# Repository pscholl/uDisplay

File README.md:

bluetoothdisplay
================

Miniature Bluetooth Display

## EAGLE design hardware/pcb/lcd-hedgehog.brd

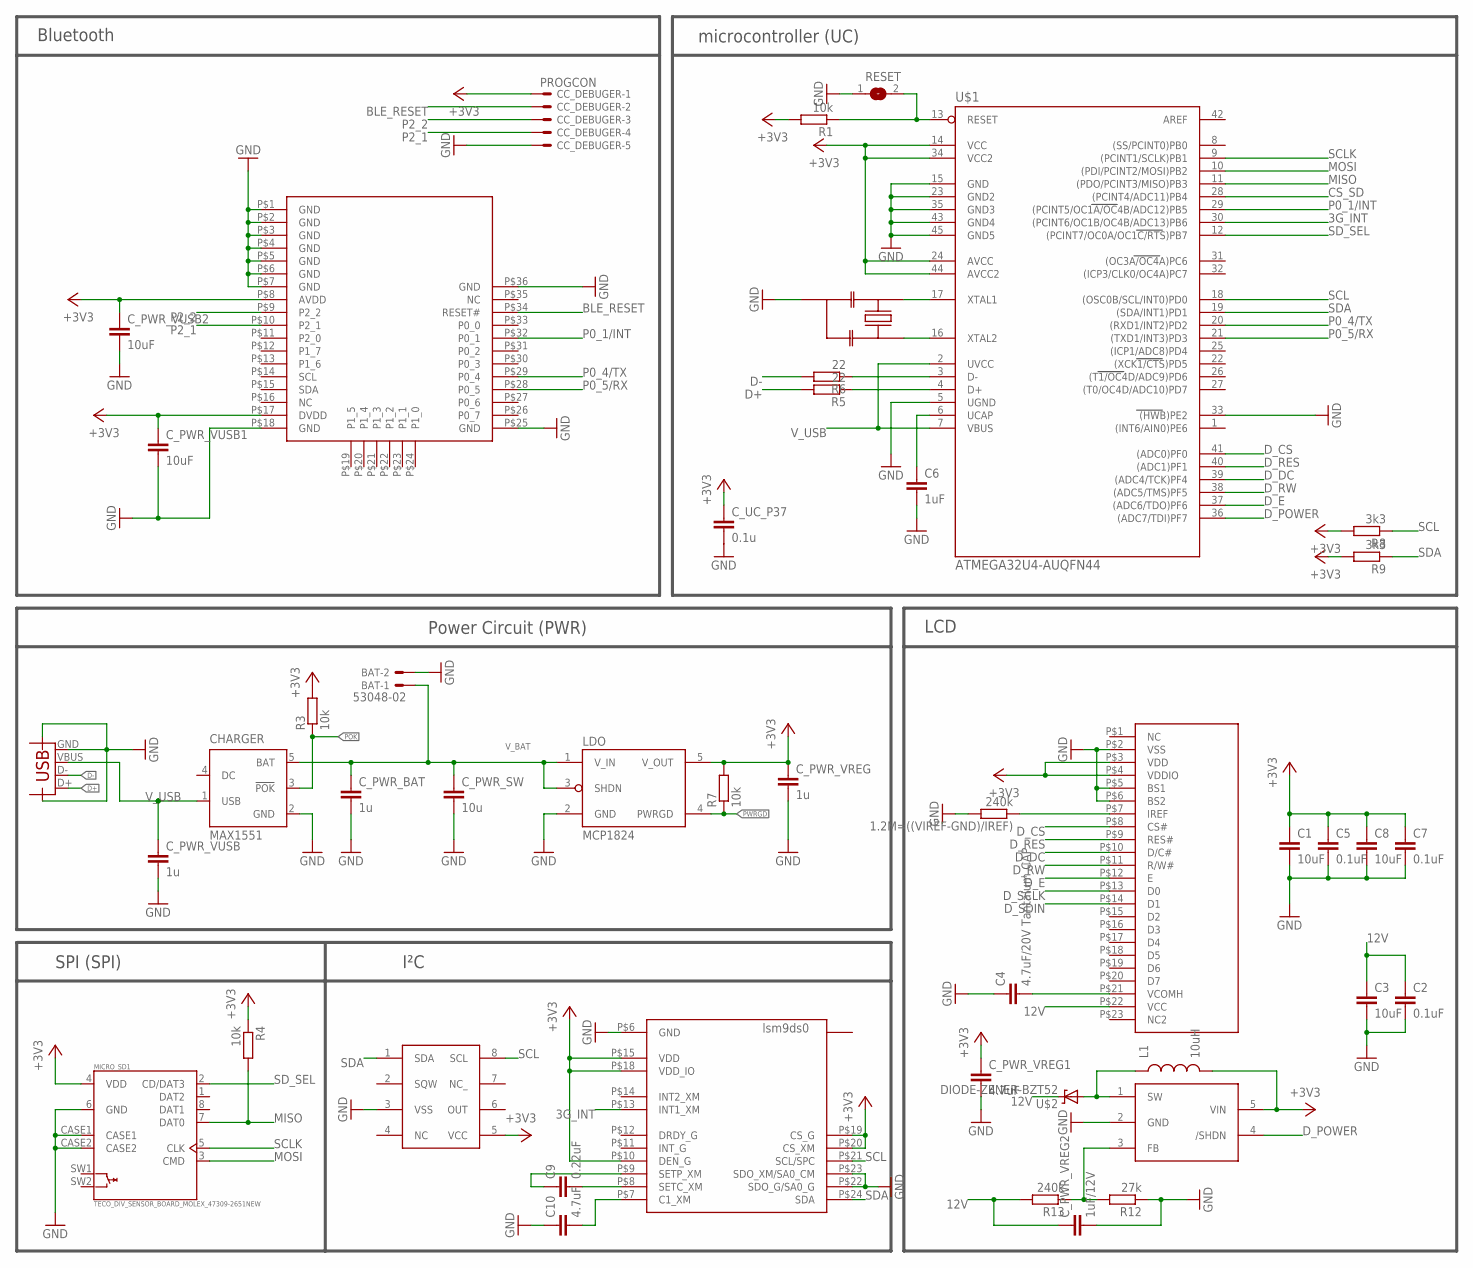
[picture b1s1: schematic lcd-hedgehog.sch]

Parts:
1.2M=((VIREF-GND)/IREF): 240k; R0603
12MHZ_RESONATOR: RESONATORPRQC-S; PRQC
BAT: 53048-02
C1, C3, C8: 10uF; C0603K
C2, C5, C7: 0.1uF; C0603K
C4: 4.7uF/20V Tantalum CAP; C0603K
C6: 1uF; C0603K
C9: 0.22uF; C0603K
C10: 4.7uF; C0603K
CC_DEBUGER: PROGCON; 53047-05-OCT
CHARGER: MAX1551; SOT23-5L
C_PWR_BAT: 1u; C0603K
C_PWR_SW: 10u; C0805K
C_PWR_VREG: 1u; C0603K
C_PWR_VREG1: 4.7uF; C0603K
C_PWR_VREG2: 1uF/12V; C0603K
C_PWR_VUSB: 1u; C0603K
C_PWR_VUSB1, C_PWR_VUSB2: 10uF; C0603K
C_UC_P37: 0.1u; C0603K
L1: 10uH; SPARKFUN_0603
LDO: MCP1824; SOT-23-5
MICRO_SD1: TECO_DIV_SENSOR_BOARD_MOLEX_47309-2651NEW; TECO_DIV_SENSOR_BOARD_MOLEX_47309-2651
R1, R3, R4, R7: 10k; R0603
R5, R6: 22; R0603
R8, R9: 3k3; R0603
R12: 27k; R0603
R13: 240k; R0603
RESET: SJ
U$1: ATMEGA32U4-AUQFN44; QFN44
U$2: DIODE-ZENER-BZT52; SOD-323
U$3: STUFF_M41T62; STUFF_M41T62LC6F
U$4: SFV23
U$5: LM2703; SOT-23-5
U$6: BLE113-A
U$7: LSM9D; LGA4X4
X1: SPARKFUN_USB-MICROB

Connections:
3G_INT: U$1.30 ((PCINT6/OC1B/OC4B/ADC13)PB6), U$7.P$13 (INT1_XM)
12V: C2.1, C3.1, C_PWR_VREG2.1, R13.2, U$2.1 (C), U$4.P$22 (VCC)
+3V3: C1.1, C5.1, C7.1, C8.1, CC_DEBUGER.1, C_PWR_VREG.1, C_PWR_VREG1.1, C_PWR_VUSB1.1, C_PWR_VUSB2.1, C_UC_P37.1, L1.2, LDO.5 (V_OUT), MICRO_SD1.4 (VDD), R1.2, R3.2, R4.1, R7.2, R8.2, R9.2, U$1.14 (VCC), U$1.24 (AVCC), U$1.34 (VCC2), U$1.44 (AVCC2), U$3.5 (VCC), U$4.P$3 (VDD), U$4.P$4 (VDDIO), U$5.5 (VIN), U$6.P$8 (AVDD), U$6.P$17 (DVDD), U$7.P$10 (DEN_G), U$7.P$15 (VDD), U$7.P$18 (VDD_IO), U$7.P$19 (CS_G), U$7.P$20 (CS_XM)
BLE_RESET: CC_DEBUGER.2, U$6.P$34 (RESET#)
CS_SD: U$1.28 ((PCINT4/ADC11)PB4)
D+: R5.2, X1.D+
D-: R6.2, X1.D-
D_CS: U$1.41 ((ADC0)PF0), U$4.P$8 (CS#)
D_DC: U$1.39 ((ADC4/TCK)PF4), U$4.P$10 (D/C#)
D_E: U$1.37 ((ADC6/TDO)PF6), U$4.P$12 (E)
D_POWER: U$1.36 ((ADC7/TDI)PF7), U$5.4 (/SHDN)
D_RES: U$1.40 ((ADC1)PF1), U$4.P$9 (RES#)
D_RW: U$1.38 ((ADC5/TMS)PF5), U$4.P$11 (R/W#)
D_SCLK: U$4.P$13 (D0)
D_SDIN: U$4.P$14 (D1)
GND: 1.2M=((VIREF-GND)/IREF).2, 12MHZ_RESONATOR.GND, BAT.2, C1.2, C2.2, C3.2, C4.1, C5.2, C6.2, C7.2, C8.2, C10.1, CC_DEBUGER.5, CHARGER.2 (GND), C_PWR_BAT.2, C_PWR_SW.2, C_PWR_VREG.2, C_PWR_VREG1.2, C_PWR_VREG2.2, C_PWR_VUSB.2, C_PWR_VUSB1.2, C_PWR_VUSB2.2, C_UC_P37.2, LDO.2 (GND), MICRO_SD1.6 (GND), MICRO_SD1.CASE1, MICRO_SD1.CASE2, R12.1, RESET.1, U$1.5 (UGND), U$1.15 (GND), U$1.23 (GND2), U$1.33 ((HWB)PE2), U$1.35 (GND3), U$1.43 (GND4), U$1.45 (GND5), U$3.3 (VSS), U$4.P$2 (VSS), U$4.P$5 (BS1), U$4.P$6 (BS2), U$5.2 (GND), U$6.P$1 (GND), U$6.P$2 (GND), U$6.P$3 (GND), U$6.P$4 (GND), U$6.P$5 (GND), U$6.P$6 (GND), U$6.P$7 (GND), U$6.P$18 (GND), U$6.P$25 (GND), U$6.P$36 (GND), U$7.P$5 (GND), U$7.P$22 (SDO_G/SA0_G), U$7.P$23 (SDO_XM/SA0_CM), X1.GND, X1.GND@2 (CASE), X1.GND@3 (CASE)
MISO: MICRO_SD1.7 (DAT0), R4.2, U$1.11 ((PDO/PCINT3/MISO)PB3)
MOSI: MICRO_SD1.3 (CMD), U$1.10 ((PDI/PCINT2/MOSI)PB2)
unnamed: R1.1, RESET.2, U$1.13 (RESET)
unnamed: 12MHZ_RESONATOR.2, U$1.17 (XTAL1)
unnamed: 12MHZ_RESONATOR.1, U$1.16 (XTAL2)
unnamed: R6.1, U$1.3 (D-)
unnamed: R5.1, U$1.4 (D+)
unnamed: C9.2, U$7.P$8 (SETC_XM)
unnamed: C9.1, U$7.P$9 (SETP_XM)
unnamed: C10.2, U$7.P$7 (C1_XM)
unnamed: C6.1, U$1.6 (UCAP)
unnamed: R12.2, R13.1, U$5.3 (FB)
unnamed: L1.1, U$2.2 (A), U$5.1 (SW)
unnamed: C4.2, U$4.P$21 (VCOMH)
unnamed: 1.2M=((VIREF-GND)/IREF).1, U$4.P$7 (IREF)
P0_1/INT: U$1.29 ((PCINT5/OC1A/OC4B/ADC12)PB5), U$6.P$32 (P0_1)
P0_4/TX: U$1.20 ((RXD1/INT2)PD2), U$6.P$29 (P0_4)
P0_5/RX: U$1.21 ((TXD1/INT3)PD3), U$6.P$28 (P0_5)
P2_1: CC_DEBUGER.4, U$6.P$10 (P2_1)
P2_2: CC_DEBUGER.3, U$6.P$9 (P2_2)
POK: CHARGER.3 (!POK), R3.1
PWRGD: LDO.4 (PWRGD), R7.1
SCL: R8.1, U$1.18 ((OSC0B/SCL/INT0)PD0), U$3.8 (SCL), U$7.P$21 (SCL/SPC)
SCLK: MICRO_SD1.5 (CLK), U$1.9 ((PCINT1/SCLK)PB1)
SDA: R9.1, U$1.19 ((SDA/INT1)PD1), U$3.1 (SDA), U$7.P$24 (SDA)
SD_SEL: MICRO_SD1.2 (CD/DAT3), U$1.12 ((PCINT7/OC0A/OC1C/RTS)PB7)
V_BAT: BAT.1, CHARGER.5 (BAT), C_PWR_BAT.1, C_PWR_SW.1, LDO.1 (V_IN), LDO.3 (SHDN)
V_USB: CHARGER.1 (USB), C_PWR_VUSB.1, U$1.2 (UVCC), U$1.7 (VBUS), X1.VBUS

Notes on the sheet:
Power Circuit (PWR)
SPI (SPI)
microcontroller (UC)
LCD
Bluetooth
I²C

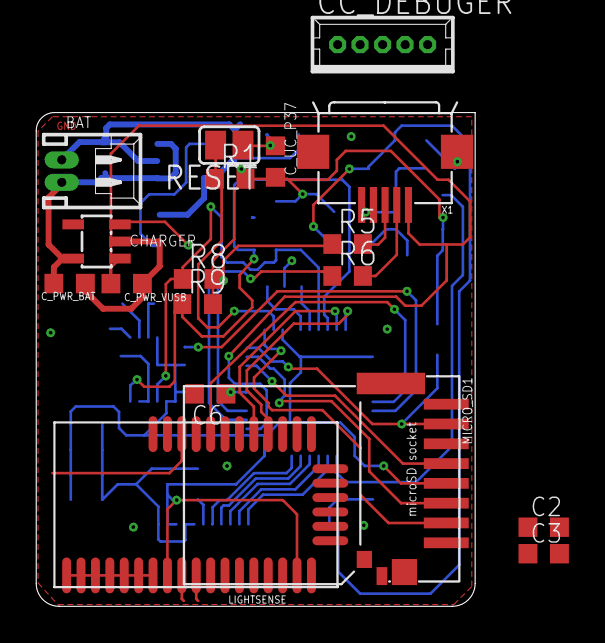
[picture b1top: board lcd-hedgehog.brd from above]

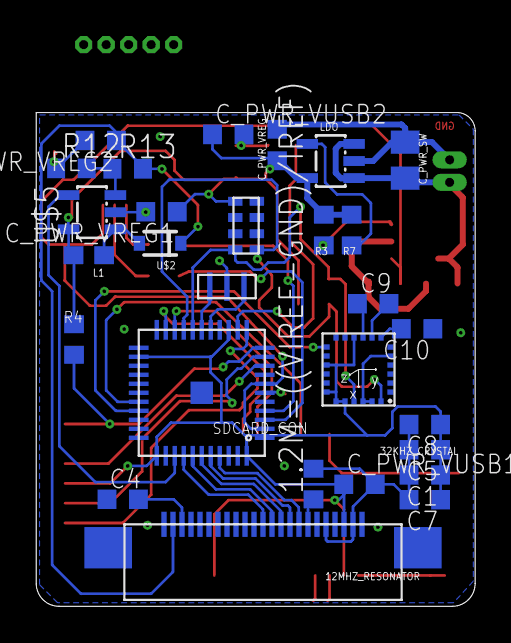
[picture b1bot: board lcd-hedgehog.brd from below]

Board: 2 copper layers, 24.4 x 27.4 mm, 46 parts (28 on the bottom side), 41 nets.

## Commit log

2013-11-01 add datasheets
2013-11-01 more datasheets
2013-11-06 initial pcb import
2013-11-06 added ble
2013-11-18 added some wiring
2013-11-22 connected IMU
2013-11-22 added Grid Eye
2013-11-22 added 12V power circuit2
2013-11-28 connected Display & first placement
2013-12-01 updated brd

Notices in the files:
parts and their libraries:
SparkFun-DiscreteSemi: Licensing: CC v3.0 Share-Alike You are welcome to use this library for commercial purposes.
